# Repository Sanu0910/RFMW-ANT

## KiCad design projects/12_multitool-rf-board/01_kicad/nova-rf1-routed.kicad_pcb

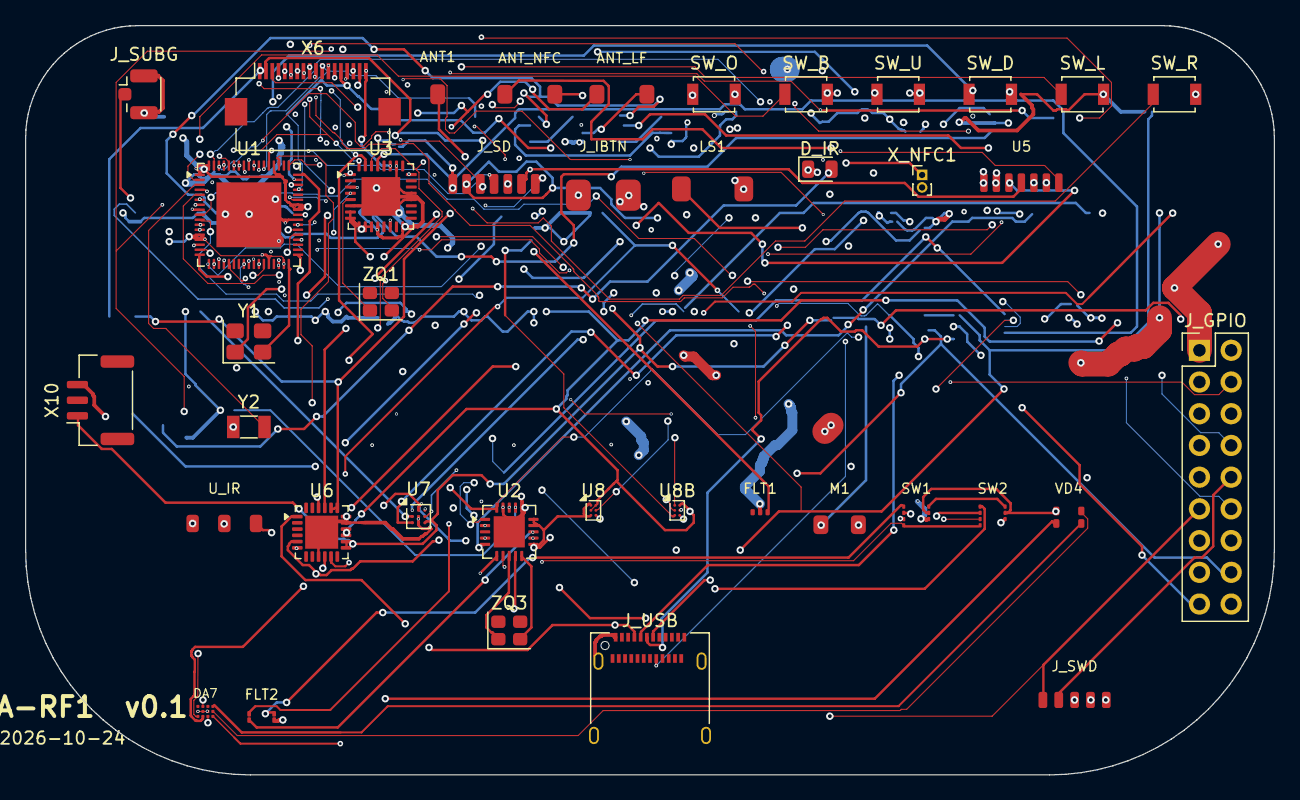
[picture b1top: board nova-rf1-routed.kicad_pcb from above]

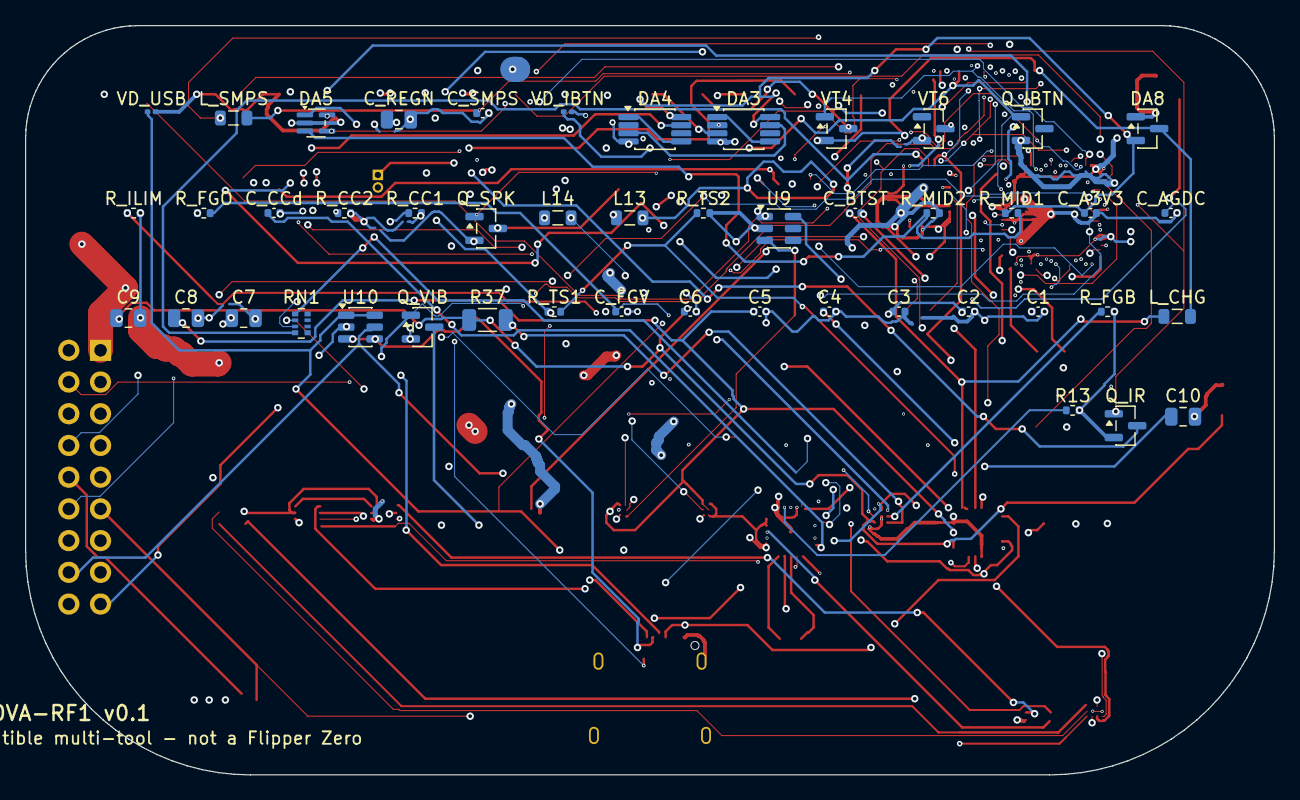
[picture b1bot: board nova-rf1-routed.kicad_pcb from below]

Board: 4 copper layers, 100.0 x 60.0 mm, 87 parts (47 on the bottom side), 104 nets.

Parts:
ANT1: 2.4GHz; Antenna_Chip
ANT_LF: 125kHz coil; RFID_125k_Coil
ANT_NFC: 13.56MHz loop; NFC_Loop_Antenna
C1, C2, C3, C4, C5, C6: 100nF; C_0402_1005Metric
C7, C8, C9, C10: 10uF; C_0805_2012Metric
C_A3V3: 1uF; C_0402_1005Metric
C_AGDC: 1uF; C_0402_1005Metric
C_BTST: 47nF; C_0402_1005Metric
C_CCd: 100nF; C_0402_1005Metric
C_FGV: 2.2uF; C_0402_1005Metric
C_REGN: 4.7uF; C_0805_2012Metric
C_SMPS: 2.2uF; C_0402_1005Metric
DA3, DA4: LMV358; VSSOP-8_3x3mm_P0.65mm
DA5: LMV331; SOT-353_SC-70-5
DA7: LP5562; LP5562_DSBGA12
DA8: RS3221-3.3; SOT-23
D_IR: IR LED x3; LED_0805_2012Metric
FLT1: BLE filter; RF_filter
FLT2: balun; Johanson_0310_Balun
J_GPIO: header 2x9; PinHeader_2x09_P2.54mm_Vertical
J_IBTN: iButton; iButton_Contacts
J_SD: microSD; microSD_7p
J_SUBG: ANT; U.FL_Hirose_U.FL-R-SMT-1_Vertical
J_SWD: SWD; TagConnect_TC2030
J_USB: USB-C; USB_C_Receptacle_Amphenol_12401610E4-2A
L13, L14: 470nH; L_0805_2012Metric
LS1: speaker; Speaker_2p
L_CHG: 2.2uH; L_0805_2012Metric
L_SMPS: 10uH; L_0805_2012Metric
M1: vibro; Vibro_2p
Q_IBTN: 1W driver; SOT-23
Q_IR: drive; SOT-23
Q_SPK: drive; SOT-23
Q_VIB: drive; SOT-23
R13: 56k; R_0402_1005Metric
R37: 10m; R_1206_3216Metric
RN1: 51x4; R_Array_Convex_4x0402
R_CC1, R_CC2: 5.1k; R_0402_1005Metric
R_FGB: 10k; R_0402_1005Metric
R_FGO: 10k; R_0402_1005Metric
R_ILIM: 1.1k; R_0402_1005Metric
R_MID1, R_MID2: 33k; R_0402_1005Metric
R_TS1: 5.23k; R_0402_1005Metric
R_TS2: 30.31k; R_0402_1005Metric
SW1, SW2: RFswitch; RF_Switch_TSNP9
SW_B: tact; SW_SPST_B3U-1000P
SW_D: tact; SW_SPST_B3U-1000P
SW_L: tact; SW_SPST_B3U-1000P
SW_O: tact; SW_SPST_B3U-1000P
SW_R: tact; SW_SPST_B3U-1000P
SW_U: tact; SW_SPST_B3U-1000P
U1: STM32WB55RG; QFN-68-1EP_8x8mm_P0.4mm_EP5.2x5.2mm
U2: CC1101; QFN-20-1EP_4x4mm_P0.5mm_EP2.5x2.5mm
U3: ST25R3916; QFN-32-1EP_5x5mm_P0.5mm_EP3.1x3.1mm
U5: ST7565R; Display_ST7565_FFC
U6: BQ25896; QFN-24-1EP_4x4mm_P0.5mm_EP2.65x2.65mm
U7: BQ27220; BGA-9_1.6x1.6mm_Layout3x3_P0.5mm
U8, U8B: LM3281; Texas_DSBGA-6_0.76x1.16mm_Layout2x3_P0.4mm
U9: loadsw; SOT-23-6
U10: ESD; SOT-23-6
U_IR: IR RX; TSOP_IR_3p
VD4: RGB LED; LED_RGB_4p
VD_IBTN: ESD; R_0201_0603Metric
VD_USB: ESD; R_0201_0603Metric
VT4: coildrv P; SOT-23
VT6: coildrv N; SOT-23
X6: FFC 18p; Hirose_FH12-18S-0.5SH_1x18-1MP_P0.50mm_Horizontal
X10: BAT+NTC; JST_GH_SM03B-GHS-TB_1x03-1MP_P1.25mm_Horizontal
X_NFC1: ANT conn; PinHeader_1x02_P1.00mm_Vertical
Y1: 32MHz; Crystal_SMD_3225-4Pin_3.2x2.5mm
Y2: 32.768kHz; Crystal_SMD_3215-2Pin_3.2x1.5mm
ZQ1: 27.12MHz; Crystal_SMD_2520-4Pin_2.5x2.0mm
ZQ3: 26MHz; Crystal_SMD_2520-4Pin_2.5x2.0mm

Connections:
+3V3: C1.1, C2.1, C3.1, C7.1, DA7.A2, DA7.C3, J_GPIO.1, J_SD.VDD, J_SWD.VCC, L13.2, SW1.VDD, SW2.VDD, U1.1, U1.13, U1.14, U1.30, U1.33, U1.44, U1.45, U1.55, U1.68, U2.4, U2.9, U2.11, U2.14, U2.15, U2.18, U3.1, U3.3, U3.7, U3.8, U3.9, U3.10, U3.11, U3.14, U5.VDD, U8.A1, U8.C1, U9.1, U_IR.VS, VD4.A
+3V3_EXT: L14.2, U8B.A1, X6.3
+3V3_PERIPH: C4.1, C10.1, U9.6
A3V3: C_A3V3.1, DA3.8, DA4.8, DA5.5, DA8.2, R_MID1.1
BLE_ANT: ANT1.1, FLT1.OUT
BTN_BACK: SW_B.1, U1.2
BTN_DOWN: SW_D.1, U1.50
BTN_LEFT: SW_L.1, U1.29
BTN_OK: SW_O.1, U1.5
BTN_RIGHT: SW_R.1, U1.46
BTN_UP: SW_U.1, U1.28
CC1101_CS: U1.61, U2.7
CC1101_GDO0: U1.16, U2.6
CC_DCOUPL: C_CCd.1, U2.5
CC_RBIAS: R13.1, U2.17
CC_XO1: U2.8, ZQ3.1
CC_XO2: U2.10, ZQ3.2
CHG_BTST: C_BTST.2, U6.21
CHG_ILIM: R_ILIM.1, U6.10
CHG_REGN: C_REGN.1, R_TS1.1, U6.22
CHG_SW: C_BTST.1, L_CHG.1, U6.19, U6.20
CHG_TS: R_TS1.2, R_TS2.1, U6.11
DISP_CS: U1.59, U5.CS
DISP_DI: U1.39, U5.A0
DISP_RST: U1.38, U5.RST
EXT_PA4: J_GPIO.4, U1.19
EXT_PA6: J_GPIO.3, U1.21
EXT_PA7: J_GPIO.2, U1.22
EXT_PB2: J_GPIO.6, U1.27
EXT_PB3: J_GPIO.5, U1.63
EXT_PC0: J_GPIO.9, U1.9
EXT_PC1: J_GPIO.8, U1.10
EXT_PC3: J_GPIO.7, U1.12
FG_BIN: R_FGB.1, U7.B1
FG_GPOUT: R_FGO.1, U7.A1
FG_VDD: C_FGV.1, R_FGO.2, U7.B3
GND: C1.2, C2.2, C3.2, C4.2, C5.2, C6.2, C7.2, C8.2, C9.2, C10.2, C_A3V3.2, C_AGDC.2, C_CCd.2, C_FGV.2, C_REGN.2, C_SMPS.2, DA3.4, DA4.4, DA5.2, DA7.B1, DA7.B2, DA7.B3, DA8.1, D_IR.1, FLT1.GND, FLT2.GND, J_GPIO.18, J_IBTN.GND, J_SD.VSS, J_SUBG.2, J_SWD.GND, J_USB.A1, J_USB.S1, LS1.-, M1.-, Q_IBTN.2, Q_IR.2, Q_SPK.2, Q_VIB.2, R13.2, R_CC1.2, R_CC2.2, R_FGB.2, R_ILIM.2, R_MID2.2, R_TS2.2, SW1.GND, SW2.GND, SW_B.2, SW_D.2, SW_L.2, SW_O.2, SW_R.2, SW_U.2, U1.32, U1.42, U1.69, U2.16, U2.19, U2.21, U3.6, U3.12, U3.16, U3.20, U3.21, U3.26, U3.33, U5.VSS, U6.9, U6.17, U6.18, U6.25, U7.B2, U7.C2, U8.C2, U8B.C2, U9.2, U10.2, U_IR.GND, VD_IBTN.2, VD_USB.2, VT6.2, X6.6, X6.8, X10.3
HSE_IN: U1.35, Y1.1
HSE_OUT: U1.34, Y1.2
I2C_PWR_SCL: DA7.C2, J_GPIO.15, U1.24, U6.5, U7.A3
I2C_PWR_SDA: DA7.C1, J_GPIO.14, U1.51, U6.6, U7.A2
IBTN: J_IBTN.DATA, Q_IBTN.1, U1.48, VD_IBTN.1, X6.14
IR_LED_A: D_IR.2, Q_IR.3
IR_RX: U1.15, U_IR.OUT, X6.17
IR_TX: Q_IR.1, U1.7, X6.16
LED_B: DA7.A4, VD4.B
LED_G: DA7.B4, VD4.G
LED_R: DA7.C4, VD4.R
LF_A1: DA3.1, DA3.5
LF_A2: DA3.7, DA4.3
LF_A3: DA4.1, DA4.5
LF_COIL_P: ANT_LF.1, VT4.3, VT6.3
LF_ENV: DA4.7, DA5.1
LF_MID: DA3.2, DA5.3, R_MID1.2, R_MID2.1
LF_RX: ANT_LF.2, DA3.3
LSE_IN: U1.3, Y2.1
LSE_OUT: U1.4, Y2.2
NFC_AGDC: C_AGDC.1, U3.24
NFC_ANT_N: ANT_NFC.2, X_NFC1.2
NFC_ANT_P: ANT_NFC.1, X_NFC1.1
NFC_CS: RN1.4, U1.40, U3.29, X6.4
NFC_XTAL1: U3.5, ZQ1.1
NFC_XTAL2: U3.4, ZQ1.2
NRST: J_SWD.NRST, U1.8
PERIPH_EN: U1.18, U8B.C1, U9.3
RFID_CARRIER: U1.17, U3.27, X6.12, X6.18
RFID_CARRIER_OUT: U1.57, VT4.1, X6.11
RFID_RF_IN: DA5.4, U1.26, X6.5
RF_SW_0: SW1.V1, SW2.V1, U1.25
RF_SW_1: SW1.V2, SW2.V2
SD_CD: J_SD.CD, U1.58
SD_CS: J_SD.CS, U1.60
SMPS_FB: C_SMPS.1, L_SMPS.2, U1.41
SMPS_LX: L_SMPS.1, U1.43
SPEAKER: Q_SPK.1, U1.6, X6.15
SPI_D_MISO: J_SD.DO, U1.11
SPI_D_MOSI: J_SD.DI, U1.49, U5.SI
SPI_D_SCK: J_SD.CLK, U1.62, U5.SCL
SPI_R_MISO: RN1.2, U1.64, U2.2, U3.32, X6.9
SPI_R_MOSI: RN1.3, U1.65, U2.20, U3.31, X6.13
SPI_R_SCK: RN1.1, U1.20, U2.1, U3.30, X6.7
SPK_DRV: LS1.+, Q_SPK.3
SUBG_ANT: J_SUBG.1, SW2.RFin
SUBG_F1: SW1.RF1, SW2.RF1
SUBG_F2: SW1.RF2, SW2.RF2
SUBG_RF_N: FLT2.BAL2, U2.13
SUBG_RF_P: FLT2.BAL1, U2.12
SUBG_SE: FLT2.UNBAL, SW1.RFin
SWCLK: J_GPIO.10, J_SWD.SWCLK, U1.56
SWDIO: J_GPIO.11, J_SWD.SWDIO, U1.54
SW_L13: L13.1, U8.B2
SW_L14: L14.1, U8B.B2
UART_RX: J_GPIO.13, U1.67
UART_TX: J_GPIO.12, U1.66
USB_CC1: J_USB.A5, R_CC1.1
USB_CC2: J_USB.B5, R_CC2.1
USB_DM: J_USB.A7, U1.52, U10.1, U10.6, VD_USB.1
USB_DP: J_USB.A6, U1.53, U10.3, U10.4
VBAT: C6.1, C9.1, R37.1, U6.13, U6.14, U7.C3, X10.1
VBAT_SNS: R37.2, U7.C1
VBUS: J_GPIO.16, J_USB.A4, U6.1, U10.5
VIBRO: J_GPIO.17, Q_VIB.1, U1.23, X6.10
VIBRO_DRV: M1.+, Q_VIB.3
VSYS: C5.1, C8.1, DA8.3, L_CHG.2, U6.15, U6.16, U8.A2, U8.B1, U8B.A2, U8B.B1, VT4.2, X6.1, X6.2

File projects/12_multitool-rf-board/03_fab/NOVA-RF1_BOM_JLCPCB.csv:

Comment,Designator,Footprint,MPN,Manufacturer,LCSC
2.4GHz,ANT1,Antenna_Chip,1001312,Johanson,
BQ27220,U7,BGA-9_1.6x1.6mm_Layout3x3_P0.5mm,BQ27220,Texas Instruments,
2.2uF,"C_FGV,C_SMPS",C_0402_1005Metric,2.2uF,Murata,
100nF,"C1,C2,C3,C4,C5,C6,C_CCd",C_0402_1005Metric,100nF,Murata,
1uF,C_AGDC,C_0402_1005Metric,1uF,Murata,
47nF,C_BTST,C_0402_1005Metric,47nF,Murata,
4.7uF,C_REGN,C_0805_2012Metric,4.7uF,Murata,
10uF,"C10,C7,C8,C9",C_0805_2012Metric,10uF,Murata,
26MHz,ZQ3,Crystal_SMD_2520-4Pin_2.5x2.0mm,CXD2-026000000,generic,
27.12MHz,ZQ1,Crystal_SMD_2520-4Pin_2.5x2.0mm,XRCGB27M120F3M00R0,Murata,
32.768kHz,Y2,Crystal_SMD_3215-2Pin_3.2x1.5mm,ABS07-32.768KHZ,Abracon,
32MHz,Y1,Crystal_SMD_3225-4Pin_3.2x2.5mm,ABM8-32.000MHZ,Abracon,
ST7565R,U5,Display_ST7565_FFC,ST7565R,Sitronix,
FFC 18p,X6,Hirose_FH12-18S-0.5SH_1x18-1MP_P0.50mm_Horizontal,FH34SRJ-18S-0.5SH,Hirose,
BAT+NTC,X10,JST_GH_SM03B-GHS-TB_1x03-1MP_P1.25mm_Horizontal,1.25-3P,generic,
balun,FLT2,Johanson_0310_Balun,B0310J50100AHF,Johanson,
IR LED x3,D_IR,LED_0805_2012Metric,VSMY14940,Vishay,
RGB LED,VD4,LED_RGB_4p,LTST-C19HE1WT,Lite-On,
LP5562,DA7,LP5562_DSBGA12,LP5562TMX,Texas Instruments,
10uH,L_SMPS,L_0805_2012Metric,10uH,Murata,
2.2uH,L_CHG,L_0805_2012Metric,2.2uH,TDK,
470nH,"L13,L14",L_0805_2012Metric,470nH,Murata,
13.56MHz loop,ANT_NFC,NFC_Loop_Antenna,PCB spiral 1.37uH,PCB,
ANT conn,X_NFC1,PinHeader_1x02_P1.00mm_Vertical,FDX0022A1,connector,
header 2x9,J_GPIO,PinHeader_2x09_P2.54mm_Vertical,Conn_2x09,generic,
CC1101,U2,QFN-20-1EP_4x4mm_P0.5mm_EP2.5x2.5mm,CC1101RGPR,Texas Instruments,
BQ25896,U6,QFN-24-1EP_4x4mm_P0.5mm_EP2.65x2.65mm,BQ25896,Texas Instruments,
ST25R3916,U3,QFN-32-1EP_5x5mm_P0.5mm_EP3.1x3.1mm,ST25R3916-AQWT,STMicroelectronics,
STM32WB55RG,U1,QFN-68-1EP_8x8mm_P0.4mm_EP5.2x5.2mm,STM32WB55RGV6,STMicroelectronics,
125kHz coil,ANT_LF,RFID_125k_Coil,wound coil + C,discrete,
RFswitch,"SW1,SW2",RF_Switch_TSNP9,BGS13S4N9,Infineon,
BLE filter,FLT1,RF_filter,LFL182G45TC1A108,Murata,
ESD,VD_USB,R_0201_0603Metric,ESD241B1W0201,Nexperia,
ESD,VD_IBTN,R_0201_0603Metric,ESD230B1W0201,Nexperia,
56k,R13,R_0402_1005Metric,56k,Yageo,
33k,"R_MID1,R_MID2",R_0402_1005Metric,33k,Yageo,
1.1k,R_ILIM,R_0402_1005Metric,1.1k,Yageo,
5.23k,R_TS1,R_0402_1005Metric,5.23k,Yageo,
30.31k,R_TS2,R_0402_1005Metric,30.31k,Yageo,
10k,"R_FGB,R_FGO",R_0402_1005Metric,10k,Yageo,
5.1k,"R_CC1,R_CC2",R_0402_1005Metric,5.1k,Yageo,
10m,R37,R_1206_3216Metric,10mOhm,Yageo,
51x4,RN1,R_Array_Convex_4x0402,51ohm array,Yageo,
coildrv P,VT4,SOT-23,DMP2004TK,Diodes,
coildrv N,VT6,SOT-23,DMN2004TK,Diodes,
drive,"Q_IR,Q_VIB",SOT-23,2N7002,Nexperia,
1W driver,Q_IBTN,SOT-23,DMN2075U,Diodes,
drive,Q_SPK,SOT-23,DMN2058UW-7,Diodes,
RS3221-3.3,DA8,SOT-23,RS3221-3.3YF3,Runic,
loadsw,U9,SOT-23-6,TPS22917,Texas Instruments,
ESD,U10,SOT-23-6,USBLC6-2SC6,STMicroelectronics,
LMV331,DA5,SOT-353_SC-70-5,LMV331IDCKR,Texas Instruments,
tact,"SW_B,SW_D,SW_L,SW_O,SW_R,SW_U",SW_SPST_B3U-1000P,EVQ-P7,Panasonic,
speaker,LS1,Speaker_2p,BCE-MX8530A-03627,BeStar,
IR RX,U_IR,TSOP_IR_3p,TSOP75338TR,Vishay,
SWD,J_SWD,TagConnect_TC2030,Tag-Connect TC2030,TagConnect,
LM3281,"U8,U8B",Texas_DSBGA-6_0.76x1.16mm_Layout2x3_P0.4mm,LM3281YFQR,Texas Instruments,
ANT,J_SUBG,U.FL_Hirose_U.FL-R-SMT-1_Vertical,U.FL-R-SMT-1,Hirose,
USB-C,J_USB,USB_C_Receptacle_Amphenol_12401610E4-2A,TYPE-C-31-M-12,GCT,
LMV358,"DA3,DA4",VSSOP-8_3x3mm_P0.65mm,LMV358AIDGKR,Texas Instruments,
vibro,M1,Vibro_2p,coin ERM,generic,
iButton,J_IBTN,iButton_Contacts,1-Wire pads PG-2.5/3.0-SM,PCB,
microSD,J_SD,microSD_7p,DM3D-SF,Hirose,
